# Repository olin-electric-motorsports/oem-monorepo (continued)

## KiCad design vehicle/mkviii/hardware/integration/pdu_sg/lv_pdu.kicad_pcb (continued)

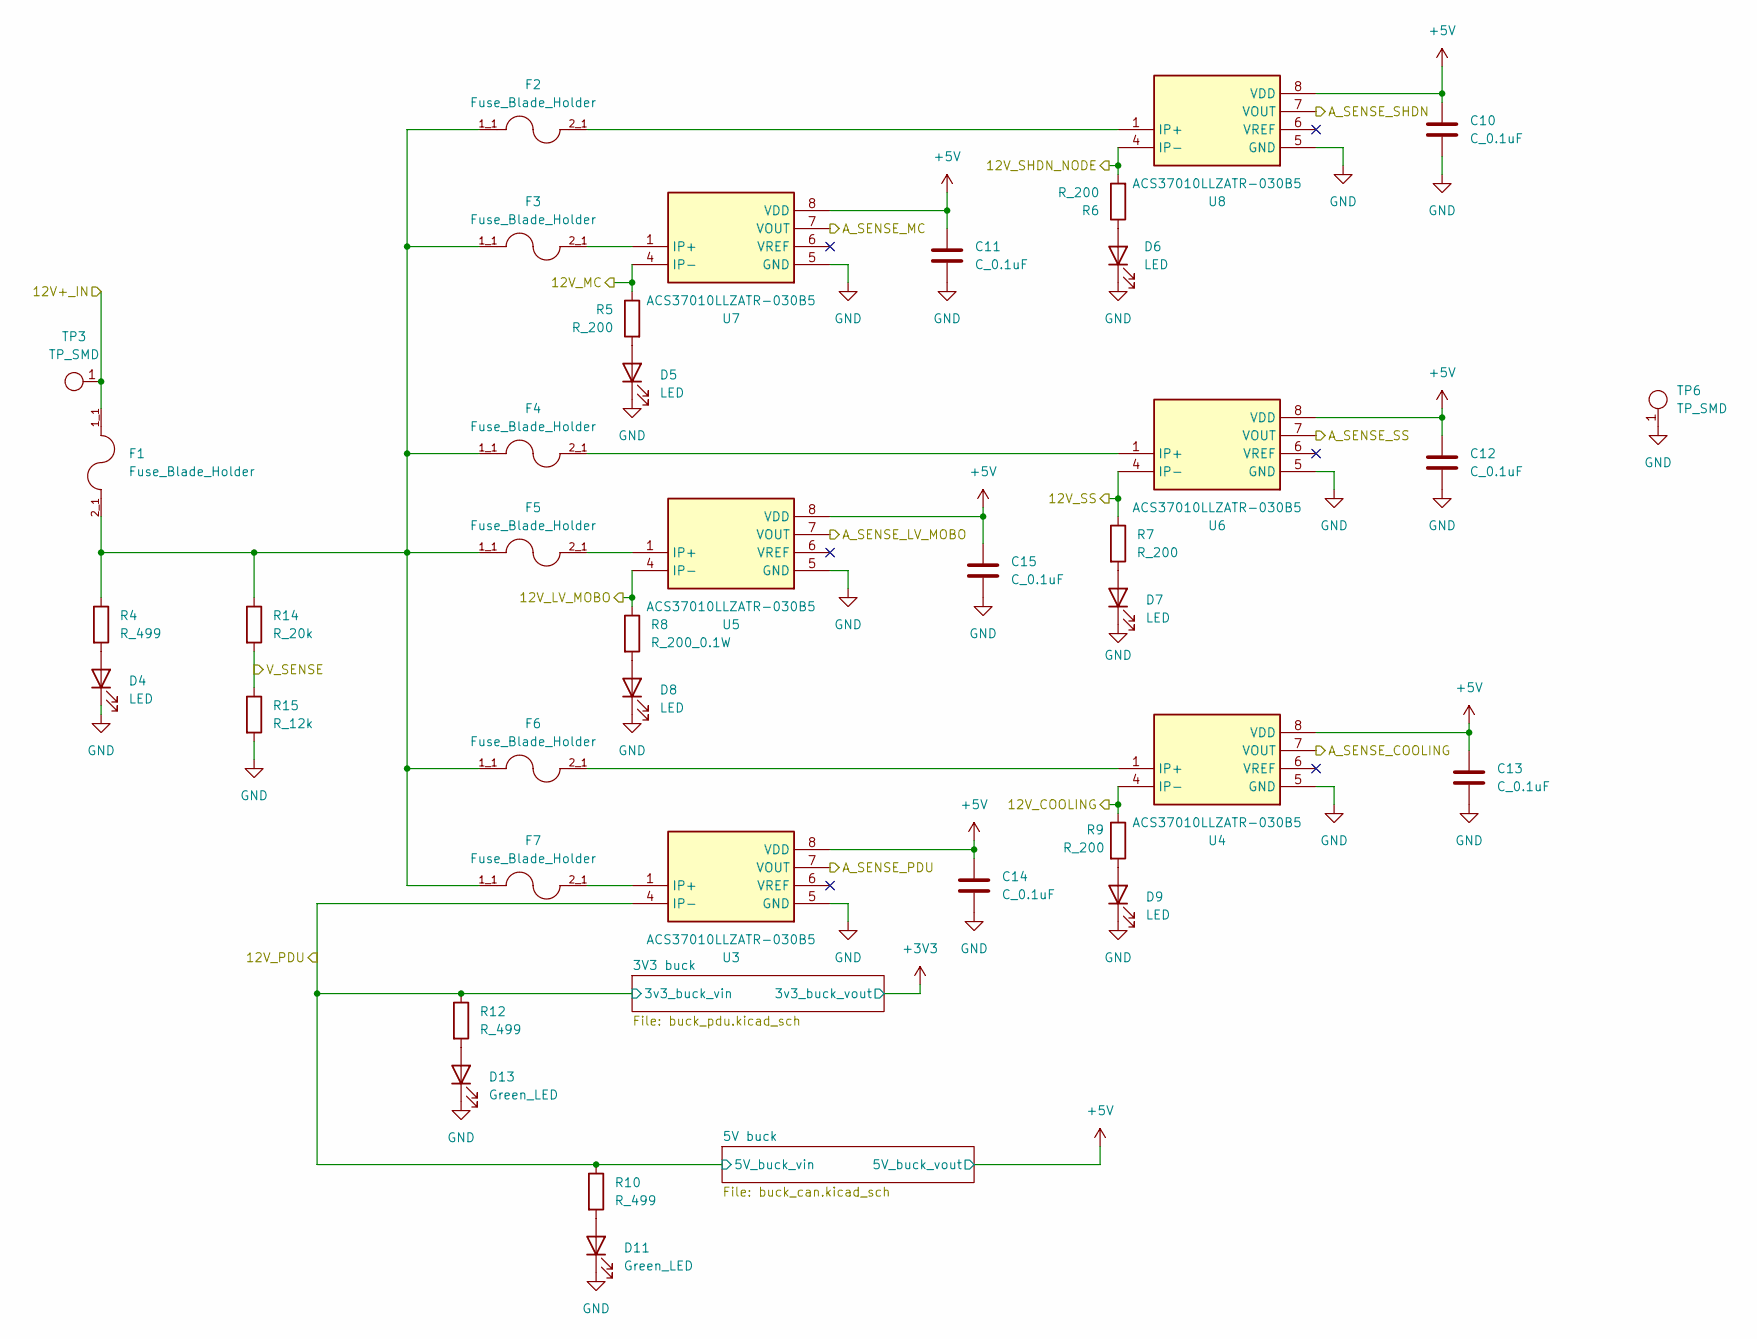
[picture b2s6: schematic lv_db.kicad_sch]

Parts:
C10, C11, C12, C13, C14, C15: C_0.1uF; C_0603_1608Metric; MPN CL10B104KB8NNWC
D4, D5, D6, D7, D8, D9: LED; D_0805_2012Metric
D11, D13: Green_LED; D_0805_2012Metric; MPN LTST-C170KGKT
F1, F2, F3, F4, F5, F6, F7: Fuse_Blade_Holder; MPN 3557-2
R4, R10, R12: R_499; R_0603_1608Metric; MPN RC0603FR-10499RL
R5, R6, R7, R9: R_200; R_0603_1608Metric; MPN WR06X2000FTL
R8: R_200_0.1W; R_0603_1608Metric; MPN WR06X2000FTL
R14: R_20k; R_0603_1608Metric; MPN SR2512JK-7W20KL
R15: R_12k; R_0603_1608Metric; MPN RMCF0603FT12K0
TP3, TP6: TP_SMD; TP_Hook_SMD; MPN 5019
U3, U4, U5, U6, U7, U8: ACS37010LLZATR-030B5; U_Current-Sensor_ACS37010LLZATR-030B5_SOIC-6; MPN ACS37010LLZATR-030B5

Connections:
+5V: C10.1, C11.1, C12.1, C13.1, C14.1, C15.1, U3.8 (VDD), U4.8 (VDD), U5.8 (VDD), U6.8 (VDD), U7.8 (VDD), U8.8 (VDD); also elsewhere on the board
+12V: F1.1, F1.1_1, F1.1_2, TP3.1; also elsewhere on the board
/12V_COOLING: R9.1, U4.4 (IP-); also elsewhere on the board
/12V_LV: R8.1, U5.4 (IP-); also elsewhere on the board
/12V_MC: R5.1, U7.4 (IP-); also elsewhere on the board
/12V_SHDN: R6.2, U8.4 (IP-); also elsewhere on the board
/12V_SS: R7.1, U6.4 (IP-); also elsewhere on the board
/AS_COOL: U4.7 (VOUT); also elsewhere on the board
/AS_LV: U5.7 (VOUT); also elsewhere on the board
/AS_MC: U7.7 (VOUT); also elsewhere on the board
/AS_PDU: U3.7 (VOUT); also elsewhere on the board
/AS_SHDN: U8.7 (VOUT); also elsewhere on the board
/AS_SS: U6.7 (VOUT); also elsewhere on the board
/V_SENSE: R14.2, R15.1; also elsewhere on the board
GND: C10.2, C11.2, C12.2, C13.2, C14.2, C15.2, D4.1 (K), D5.1 (K), D6.1 (K), D7.1 (K), D8.1 (K), D9.1 (K), D11.1 (K), D13.1 (K), R15.2, TP6.1, U3.5 (GND), U4.5 (GND), U5.5 (GND), U6.5 (GND), U7.5 (GND), U8.5 (GND); also elsewhere on the board
unnamed: D4.2 (A), R4.2
unnamed: D5.2 (A), R5.2
unnamed: D6.2 (A), R6.1
unnamed: D7.2 (A), R7.2
unnamed: D8.2 (A), R8.2
unnamed: D9.2 (A), R9.2
unnamed: D11.2 (A), R10.2
unnamed: D13.2 (A), R12.2
unnamed: F1.2, F1.2_1, F1.2_2, F2.1, F2.1_1, F2.1_2, F3.1, F3.1_1, F3.1_2, F4.1, F4.1_1, F4.1_2, F5.1, F5.1_1, F5.1_2, F6.1, F6.1_1, F6.1_2, F7.1, F7.1_1, F7.1_2, R4.1, R14.1
unnamed: F7.2, F7.2_1, F7.2_2, U3.1 (IP+)
unnamed: F6.2, F6.2_1, F6.2_2, U4.1 (IP+)
unnamed: F5.2, F5.2_1, F5.2_2, U5.1 (IP+)
unnamed: F4.2, F4.2_1, F4.2_2, U6.1 (IP+)
unnamed: F3.2, F3.2_1, F3.2_2, U7.1 (IP+)
unnamed: F2.2, F2.2_1, F2.2_2, U8.1 (IP+)

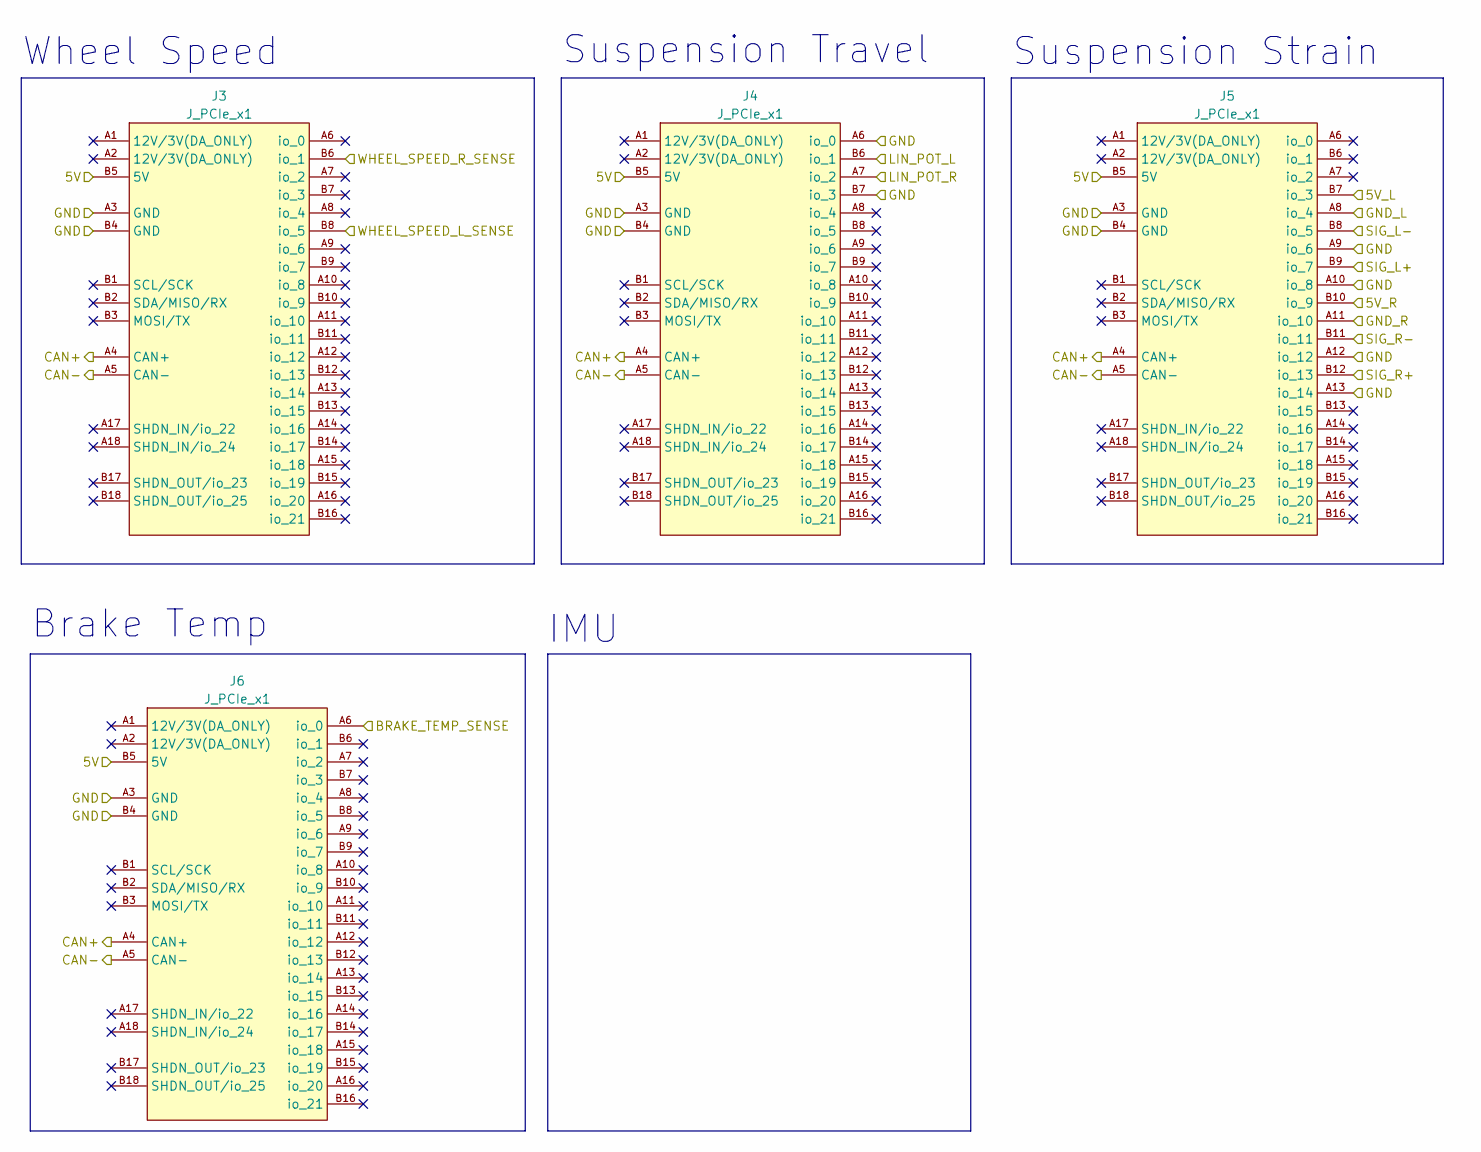
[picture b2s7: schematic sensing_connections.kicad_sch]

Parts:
J3, J4, J5, J6: J_PCIe_x1; MPN 2-1761465-1

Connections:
+5V: J3.B5 (5V), J4.B5 (5V), J5.B5 (5V), J6.B5 (5V); also elsewhere on the board
/BRAKE_TEMP_SIG: J6.A6 (io_0); also elsewhere on the board
/CAN_2+: J3.A4 (CAN+), J4.A4 (CAN+), J5.A4 (CAN+), J6.A4 (CAN+); also elsewhere on the board
/CAN_2-: J3.A5 (CAN-), J4.A5 (CAN-), J5.A5 (CAN-), J6.A5 (CAN-); also elsewhere on the board
/EXCITATION_L+: J5.B7 (io_3); also elsewhere on the board
/EXCITATION_L-: J5.A8 (io_4); also elsewhere on the board
/EXCITATION_R+: J5.B10 (io_9); also elsewhere on the board
/EXCITATION_R-: J5.A11 (io_10); also elsewhere on the board
/SIGNAL_L+: J5.B9 (io_7); also elsewhere on the board
/SIGNAL_L-: J5.B8 (io_5); also elsewhere on the board
/SIGNAL_R+: J5.B12 (io_13); also elsewhere on the board
/SIGNAL_R-: J5.B11 (io_11); also elsewhere on the board
/SUS_TRAVEL_L_SIG: J4.B6 (io_1); also elsewhere on the board
/SUS_TRAVEL_R_SIG: J4.A7 (io_2); also elsewhere on the board
/WHEEL_SPEED_L_SIG: J3.B8 (io_5)
/WHEEL_SPEED_R_SIG: J3.B6 (io_1)
GND: J3.A3 (GND), J3.B4 (GND), J4.A3 (GND), J4.A6 (io_0), J4.B4 (GND), J4.B7 (io_3), J5.A3 (GND), J5.A9 (io_6), J5.A10 (io_8), J5.A12 (io_12), J5.A13 (io_14), J5.B4 (GND), J6.A3 (GND), J6.B4 (GND); also elsewhere on the board

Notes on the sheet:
Brake Temp
Suspension Travel
IMU
Suspension Strain
Wheel Speed

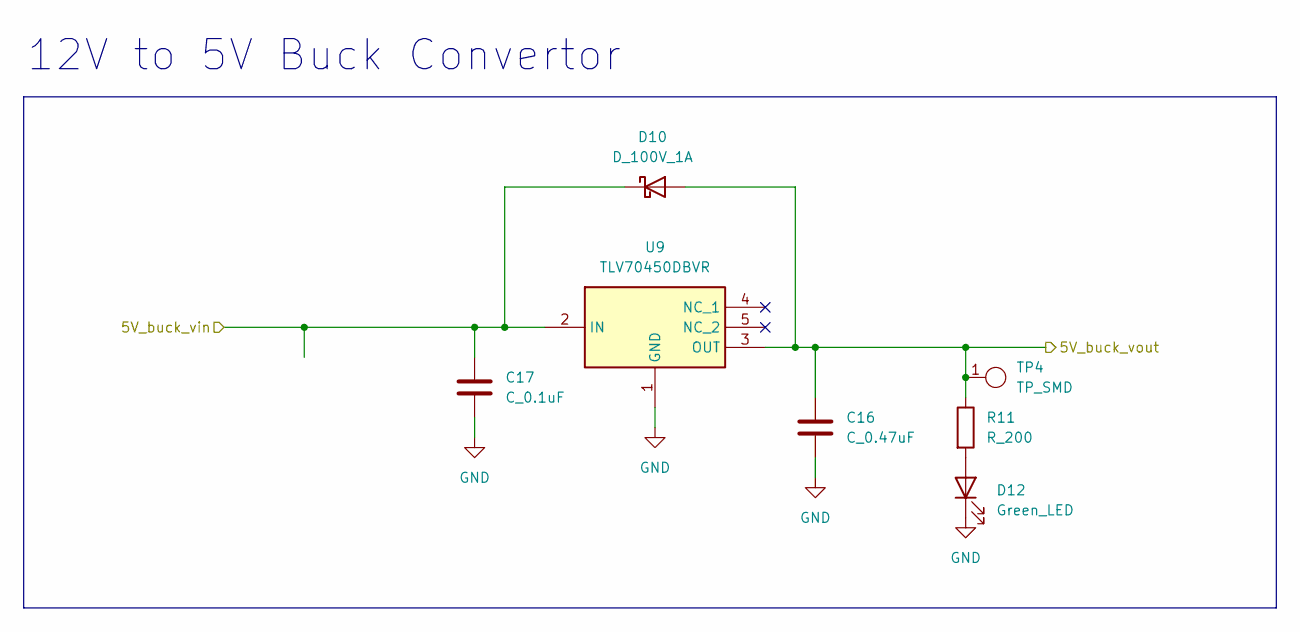
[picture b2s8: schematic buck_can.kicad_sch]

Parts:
C16: C_0.47uF; C_0603_1608Metric; MPN GRM188R71E474KA12D
C17: C_0.1uF; C_0603_1608Metric; MPN C0603C104Z4VACTU
D10: D_100V_1A; SODFL3718X102N (D_Schottky_100V_1A_SMD - SS110LW); MPN SS110LW
D12: Green_LED; D_0805_2012Metric; MPN LTST-C171KRKT
R11: R_200; R_0603_1608Metric; MPN WR06X2000FTL
TP4: TP_SMD; TP_Hook_SMD; MPN 5019
U9: TLV70450DBVR; SOT-23-5; MPN TLV70450DBVR

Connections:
+5V: C16.1, D10.2 (A), R11.1, TP4.1, U9.3 (OUT); also elsewhere on the board
GND: C16.2, C17.2, D12.1 (K), U9.1 (GND); also elsewhere on the board
unnamed: D12.2 (A), R11.2

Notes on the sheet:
12V to 5V Buck Convertor

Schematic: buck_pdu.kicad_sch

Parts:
C18: C_10uF; C_0603_1608Metric; MPN GRM188D71A106KA73D
C19, C20: C_22uF; C_0603_1608Metric; MPN CL31A226KAHNNNE
C21: C_0.1uF; C_0603_1608Metric; MPN C0603C104Z4VACTU
D14: Green_LED; D_0805_2012Metric; MPN LTST-C170KGKT
L1: L_3.9uH; IND_BOURNS_SRR5018 (L_3.9uH_2A_55m_SMD); MPN SRR5018-3R9Y
R13: R_60.4; R_0603_1608Metric; MPN RMCF0603FT60R4
TP5: TP_SMD; TP_Hook_SMD; MPN 5019
U10: AP63203WU-7; SOT-23-6; MPN AP63203WU-7

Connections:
/low voltage distribution/3V3 buck/3V3_buck_vout: C19.1, C20.1, L1.2, R13.1, TP5.1, U10.1 (FB)
GND: C18.2, C19.2, C20.2, D14.1 (K), U10.4 (GND); also elsewhere on the board
unnamed: D14.2 (A), R13.2
unnamed: C21.1, U10.6 (BST)
unnamed: C21.2, L1.1, U10.5 (SW)

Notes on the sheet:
12V to 3V3 Buck Converter

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
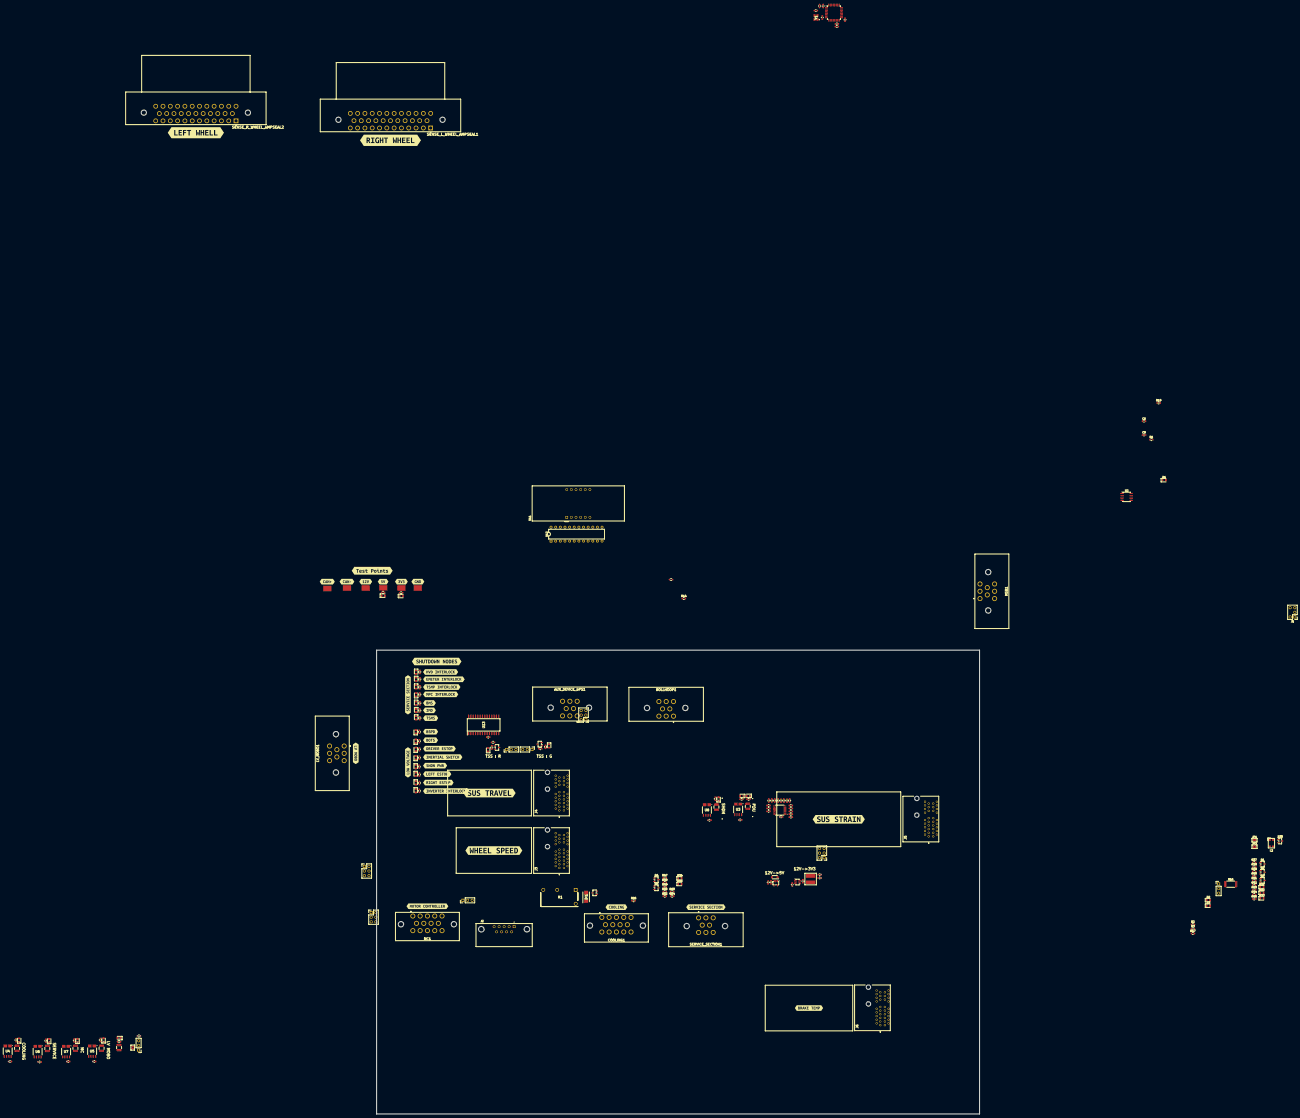
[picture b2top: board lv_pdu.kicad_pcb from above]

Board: 4 copper layers, 330.2 x 254.0 mm, 233 parts (0 on the bottom side), 167 nets.

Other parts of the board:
kibuzzard-6AF3A9EF: G***; kibuzzard-6AF3A9EF
kibuzzard-6AF3AA3E: G***; kibuzzard-6AF3AA3E
kibuzzard-6AF3AA7C: G***; kibuzzard-6AF3AA7C
kibuzzard-6AF3AA54: G***; kibuzzard-6AF3AA54
kibuzzard-6AF3AA92: G***; kibuzzard-6AF3AA92
kibuzzard-6AF3AAA2: G***; kibuzzard-6AF3AAA2
kibuzzard-6AF3AB1F: G***; kibuzzard-6AF3AB1F
kibuzzard-6AF3AB02: G***; kibuzzard-6AF3AB02
kibuzzard-6AF3AB16: G***; kibuzzard-6AF3AB16
kibuzzard-6AF3AB30: G***; kibuzzard-6AF3AB30
kibuzzard-6AF3AC5A: G***; kibuzzard-6AF3AC5A
kibuzzard-6AF3AC21: G***; kibuzzard-6AF3AC21
kibuzzard-6AF3AC46: G***; kibuzzard-6AF3AC46
kibuzzard-6AF3AC51: G***; kibuzzard-6AF3AC51
kibuzzard-6AF3AC73: G***; kibuzzard-6AF3AC73
kibuzzard-6AF3AC82: G***; kibuzzard-6AF3AC82
kibuzzard-6AF3ACA7: G***; kibuzzard-6AF3ACA7
kibuzzard-6AF3ACE3: G***; kibuzzard-6AF3ACE3
kibuzzard-6AF3AD90: G***; kibuzzard-6AF3AD90
kibuzzard-6AF3ADBE: G***; kibuzzard-6AF3ADBE
kibuzzard-6AF3ADF4: G***; kibuzzard-6AF3ADF4
kibuzzard-6AF3AE7A: G***; kibuzzard-6AF3AE7A
kibuzzard-6AF3AE17: G***; kibuzzard-6AF3AE17
kibuzzard-6AF3AEED: G***; kibuzzard-6AF3AEED
kibuzzard-6AF3AF2F: G***; kibuzzard-6AF3AF2F
kibuzzard-6AF3BEE3: G***; kibuzzard-6AF3BEE3
kibuzzard-6AF3BF1E: G***; kibuzzard-6AF3BF1E
kibuzzard-6AF3BF40: G***; kibuzzard-6AF3BF40
kibuzzard-6AF392A3: G***; kibuzzard-6AF392A3
kibuzzard-6AF392F1: G***; kibuzzard-6AF392F1
kibuzzard-6AF3934F: G***; kibuzzard-6AF3934F
kibuzzard-6AF3939E: G***; kibuzzard-6AF3939E
kibuzzard-6AF39264: G***; kibuzzard-6AF39264
kibuzzard-6AF39337: G***; kibuzzard-6AF39337
kibuzzard-6AF39365: G***; kibuzzard-6AF39365

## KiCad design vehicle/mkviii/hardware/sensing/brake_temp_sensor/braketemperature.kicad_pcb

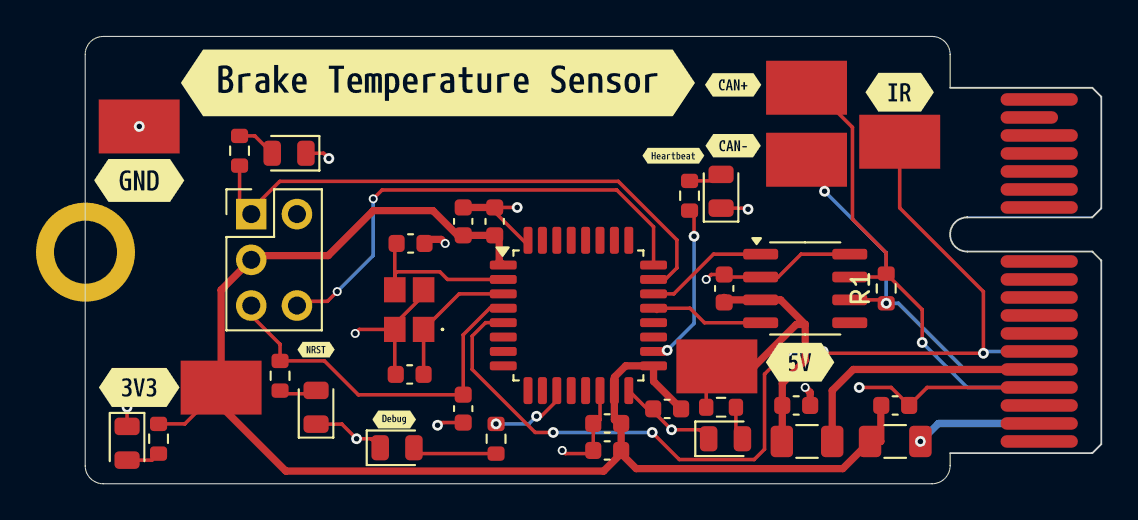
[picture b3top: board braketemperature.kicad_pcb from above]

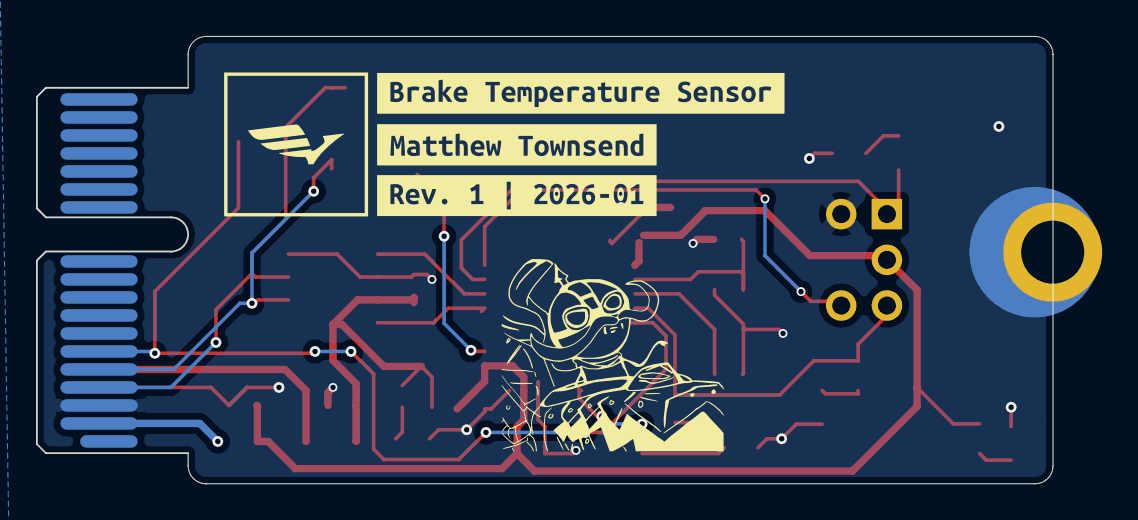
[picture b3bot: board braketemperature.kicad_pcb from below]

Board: 2 copper layers, 56.4 x 24.9 mm, 51 parts (3 on the bottom side), 23 nets.

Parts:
C1, C2, C4, C7: C_0.1uF; C_0603_1608Metric
C3: C_10nF; C_0603_1608Metric
C5: C_1uF; C_0603_1608Metric
C6: C_4.7uF; C_0603_1608Metric
C8, C9: C_30pF; C_0603_1608Metric
C10, C11: C_10uF_10V; C_0603_1608Metric
D1, D2, D3, D4, D5, D6: D_Red_LED; D_0805_2012Metric
F1, F2: F_500mA_8V; Fuse_1206_3216Metric
H1: H_MountingHole
J1: J_PCIe_x1; J_PCIe_x1_Key
J2: J_Programming_Pin_Header; J_Programming_Pin_Header_Keyed
R1: R_120; R_0603_1608Metric
R2, R3, R4, R5, R6, R7: R_1k; R_0603_1608Metric
TP1, TP2, TP3, TP4, TP5, TP6: TP_SMD; TP_Hook_SMD
U1: MCP2561-E_SN; SOIC-8_3.9x4.9mm_P1.27mm
U2: STM32G441KBT6; LQFP-32_7x7mm_P0.8mm
Y1: X_16MHz_18pF; FA238160000MBC0 (X_16MHz_18pF_SMD - FA-238_16.0000MB-C0)
kibuzzard-697E6E94: G***; kibuzzard-697E6E94
kibuzzard-697E6EEF: G***; kibuzzard-697E6EEF
kibuzzard-697E6F70: G***; kibuzzard-697E6F70
kibuzzard-697E6FE4: G***; kibuzzard-697E6FE4
kibuzzard-697F80A9: G***; kibuzzard-697F80A9
kibuzzard-697F80BA: G***; kibuzzard-697F80BA
kibuzzard-697F802E: G***; kibuzzard-697F802E
kibuzzard-69815F9D: G***; kibuzzard-69815F9D
kibuzzard-69815FEC: G***; kibuzzard-69815FEC
kibuzzard-69815FF8: G***; kibuzzard-69815FF8
kibuzzard-69816079: G***; kibuzzard-69816079
kibuzzard-69816083: G***; kibuzzard-69816083
kibuzzard-69816091: G***; kibuzzard-69816091

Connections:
+3V3: C2.1, C3.1, C4.1, C5.1, C6.1, C11.1, F2.1, J2.3, R3.1, TP3.1, U2.1 (VDD), U2.15 (VDDA), U2.17 (VDD)
+5V: C1.1, C10.1, F1.1, R2.1, TP2.1, U1.3 (VDD)
/CAN_RX: U1.4 (RXD), U2.21 ((FDCAN1_RX/GPIO_EXTI11)PA11)
/CAN_TX: U1.1 (TXD), U2.22 ((FDCAN1_TX/GPIO_EXTI12)PA12)
/Debug LED: R5.1, U2.11 ((TIM3_CH1/TIM16_CH1/GPIO_EXTI6/ADC2_IN3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)
/Heartbeat LED: R4.1, U2.18 ((TIM4_ETR/USART1_CK/GPIO_EXTI8)PA8)
/IR Output - PA0: J1.A6 (io_0), TP1.1, U2.5 ((TIM2_ETR/TIM2_CH1/GPIO_EXTI0/ADC2_IN1/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)
/NRST: C7.1, J2.4, R6.1, U2.4 ((GPIO_EXTI10)PG10-NRST)
/SWCLK: J2.5, U2.24 ((SYS_JTCK-SWCLK/GPIO_EXTI14)PA14)
/SWDIO: J2.1, R7.1, U2.23 ((SYS_JTMS-SWDIO/GPIO_EXTI13)PA13)
GND: C1.2, C2.2, C3.2, C4.2, C5.2, C6.2, C7.2, C8.2, C9.2, C10.2, C11.2, D1.1 (K), D2.1 (K), D3.1 (K), D4.1 (K), D5.1 (K), D6.1 (K), H1.1, J1.A3 (GND), J1.B4 (GND), J2.2, TP6.1, U1.2 (VSS), U1.8 (STBY), U2.14 (VSSA), U2.16 (VSS), U2.32 (VSS), Y1.2, Y1.4
unnamed: D1.2 (A), R2.2
unnamed: D2.2 (A), R3.2
unnamed: D3.2 (A), R4.2
unnamed: D4.2 (A), R5.2
unnamed: D5.2 (A), R6.2
unnamed: D6.2 (A), R7.2
unnamed: F2.2, J1.A2 (3.3V)
unnamed: F1.2, J1.B5 (5V)
unnamed: J1.A4 (CAN+), R1.2, TP4.1, U1.7 (CANH)
unnamed: J1.A5 (CAN-), R1.1, TP5.1, U1.6 (CANL)
unnamed: C9.1, U2.2 (PF0-OSC_IN), Y1.3
unnamed: C8.1, U2.3 (PF1-OSC_OUT), Y1.1

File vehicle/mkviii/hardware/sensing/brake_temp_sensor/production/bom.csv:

Designator,Footprint,Quantity,Value,LCSC Part #
"C1, C2, C4, C7",0603,4,C_0.1uF,C0603C104Z4VACTU
"C10, C11",0603,2,C_10uF_10V,GRM188D71A106KA73D
C3,0603,1,C_10nF,CL10B103KB8NNNC
C5,0603,1,C_1uF,CL10B105KA8NNNC
C6,0603,1,C_4.7uF,GRT188R61E475ME13D
"C8, C9",0603,2,C_30pF,CML0603C0G300JT50V
"D1, D2, D3, D4, D5, D6",0805,6,D_Red_LED,LTST-C171KRKT
"F1, F2",1206,2,F_500mA_8V,0ZCJ0050FF2G
J1,J_PCIe_x1_Key,1,J_PCIe_x1,2-1761465-1
J2,J_Programming_Pin_Header_Keyed,1,J_Programming_Pin_Header,
R1,0603,1,R_120,RC0603FR-13120RL
"R2, R3, R4, R5, R6, R7",0603,6,R_1k,RMCF0603FT1K00 (or ERJ-3GEYJ102V)
"TP1, TP2, TP3, TP4, TP5, TP6",TP_Hook_SMD,6,TP_SMD,5019
U1,SOIC-8_3.9x4.9mm_P1.27mm,1,MCP2561-E_SN,MCP2561-E/SN
U2,LQFP-32_7x7mm_P0.8mm,1,STM32G441KBT6,
Y1,FA238160000MBC0 (X_16MHz_18pF_SMD - FA-238_16.0000MB-C0),1,X_16MHz_18pF,FA-238 16.0000MB-C0

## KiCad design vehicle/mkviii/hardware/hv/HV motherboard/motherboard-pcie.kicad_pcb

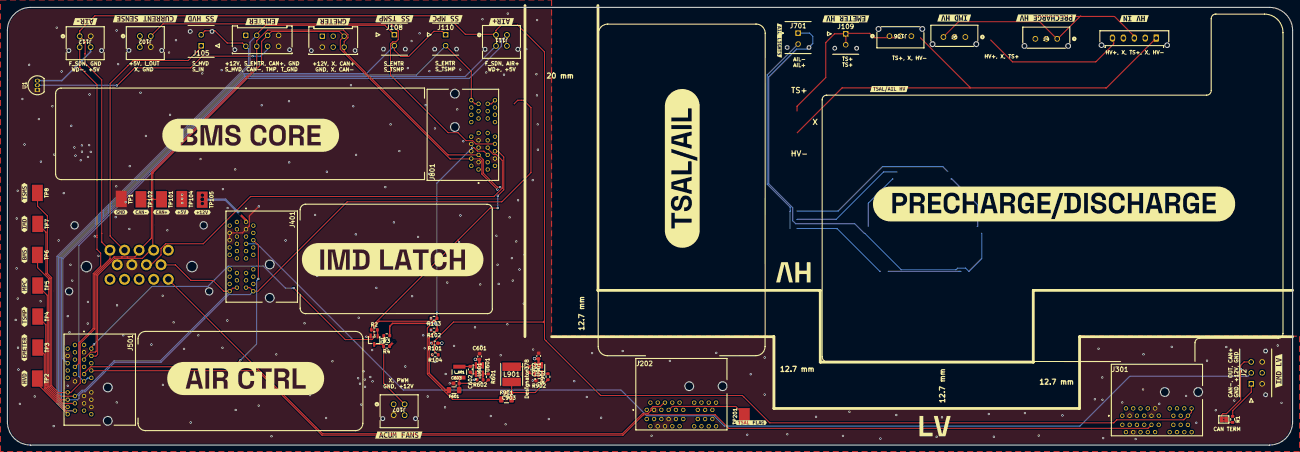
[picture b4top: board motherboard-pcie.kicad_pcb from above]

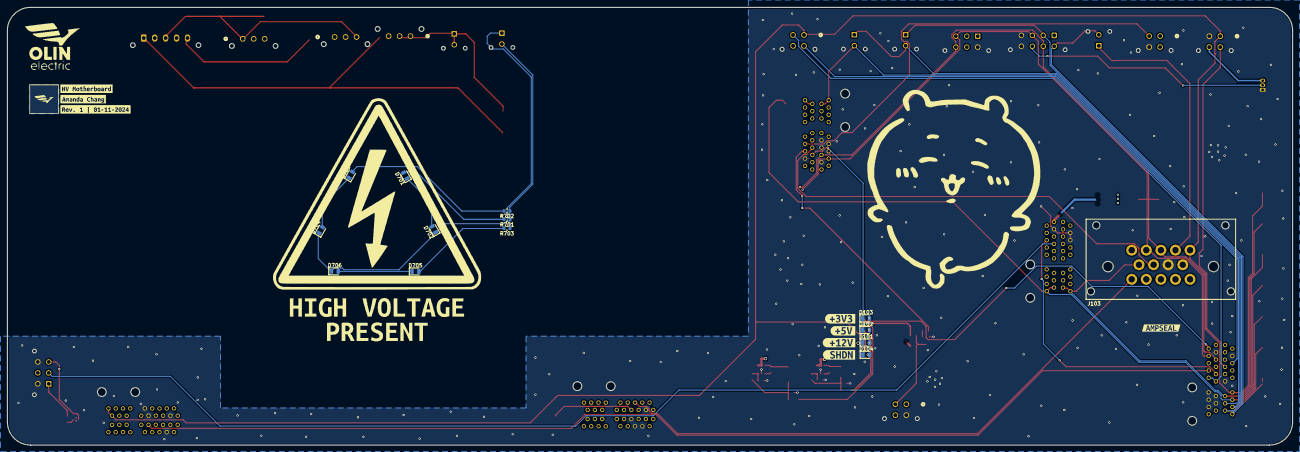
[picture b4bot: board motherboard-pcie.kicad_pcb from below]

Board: 4 copper layers, 352.4 x 120.0 mm, 121 parts (24 on the bottom side), 52 nets.

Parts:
C601, C901: C_2.2uF; C_0603_1608Metric
C602, C902: C_0.1uF; C_0603_1608Metric
C603, C903: C_10uF; C_0603_1608Metric
D101, D102: D_Green_LED; D_0805_2012Metric
D103: LED; D_0805_2012Metric
D104: D_Blue_LED; D_0805_2012Metric
D701, D702, D703, D704, D705, D706: LED_0805; D_0805_2012Metric
F601, F901: F_1.5A_63V; Fuse_1206_3216Metric
J1: Conn_02x04_Odd_Even; Molex_Micro-Fit_3.0_43045-0812_2x04_P3.00mm_Vertical
J2: 2X3; J_Molex_Header_02x03_VT - 43045-06YY_121314
J3: Conn_01x05; Molex_Micro-Fit_3.0_43650-0515_1x05_P3.00mm_Vertical
J4, J6, J106: J_Molex_Header_01x03_VT; J_Molex_Header_01x03_VT - 436500327
J102, J111, J112: AIR+; J_Molex_Header_02x02_VT - 0430450414
J103: J_Ampseal_14_VT
J105, J108, J109, J110, J701: J_Molex_Header_01x02_VT; J_Molex_Header_01x02_VT - 43045-02YY_121314
J107: ACCUM_FAN; J_Molex_Header_02x02_VT - 0430450414
J113: GMETER; Molex_Micro-Fit_3.0_43045-0612_2x03_P3.00mm_Vertical
J202, J301, J401, J501, J801: J_PCIe_x1
JP1: SolderJumper_2_Bridged; SolderJumper-2_P1.3mm_Bridged2Bar_Pad1.0x1.5mm
L901: L_3.3uH; SRN6045TA330M (L_3.3uH_5A_21m_SMD - SRN6045TA-3R3Y)
L_601: L_4.7uH; IND_ASPI-4030S-4R7M-T
Q1: SSM3K333R,LF; SOT-23-3
R1, R701, R702, R703: R_120; R_0603_1608Metric
R2, R3, R4: R_100; R_0603_1608Metric
R101, R104: R_1k; R_0603_1608Metric
R102: R_330; R_0603_1608Metric
R103: R_301; R_0603_1608Metric
R601: R_88.7k; R_0603_1608Metric
R602, R902: R_22.1k; R_0603_1608Metric
R901: R_51k; R_0603_1608Metric
TP1, TP2, TP3, TP4, TP5, TP6, TP7, TP8, TP101, TP102, TP104, TP105, TP201: TP_SMD; TP_Hook_SMD
U1: DS18B20; TO-92_Inline
U601: U_5V-Buck-Conv-1A-SOT23-6; DBV0006A-IPC_A
U901: U_3.3V-Buck-Conv-1A-SOT23-6; DBV0006A-IPC_A
kibuzzard-6AF3C239: G***; kibuzzard-6AF3C239
kibuzzard-6AF3C241: G***; kibuzzard-6AF3C241
kibuzzard-640B75B2: G***; kibuzzard-640B75B2
kibuzzard-640B76B0: G***; kibuzzard-640B76B0
kibuzzard-640B87CD: G***; kibuzzard-640B87CD
kibuzzard-640B861F: G***; kibuzzard-640B861F
kibuzzard-640B8645: G***; kibuzzard-640B8645
kibuzzard-640B8668: G***; kibuzzard-640B8668
kibuzzard-640B8680: G***; kibuzzard-640B8680
kibuzzard-677B3C3E: G***; kibuzzard-677B3C3E
kibuzzard-677B3C38: G***; kibuzzard-677B3C38
kibuzzard-677B3E90: G***; kibuzzard-677B3E90
kibuzzard-677CE749: G***; kibuzzard-677CE749
kibuzzard-677CFB84: G***; kibuzzard-677CFB84
kibuzzard-677CFB97: G***; kibuzzard-677CFB97
kibuzzard-677CFBA0: G***; kibuzzard-677CFBA0
kibuzzard-677E2BD4: G***; kibuzzard-677E2BD4
kibuzzard-677E2BDC: G***; kibuzzard-677E2BDC
kibuzzard-677E2BE2: G***; kibuzzard-677E2BE2
kibuzzard-677E2BE7: G***; kibuzzard-677E2BE7
kibuzzard-677E2BEC: G***; kibuzzard-677E2BEC
kibuzzard-677E2BF5: G***; kibuzzard-677E2BF5
kibuzzard-677E2BFE: G***; kibuzzard-677E2BFE
kibuzzard-677E26A9: G***; kibuzzard-677E26A9
kibuzzard-677E26B0: G***; kibuzzard-677E26B0
kibuzzard-677E26B5: G***; kibuzzard-677E26B5
kibuzzard-677E26BE: G***; kibuzzard-677E26BE
kibuzzard-677E26C5: G***; kibuzzard-677E26C5
kibuzzard-677E26CB: G***; kibuzzard-677E26CB
kibuzzard-677E26D4: G***; kibuzzard-677E26D4
kibuzzard-677E26ED: G***; kibuzzard-677E26ED
kibuzzard-677E335B: G***; kibuzzard-677E335B
kibuzzard-677E336E: G***; kibuzzard-677E336E
kibuzzard-677E3331: G***; kibuzzard-677E3331
kibuzzard-677E3355: G***; kibuzzard-677E3355
kibuzzard-677E3368: G***; kibuzzard-677E3368
kibuzzard-677FDCF4: G***; kibuzzard-677FDCF4
kibuzzard-6786FEE0: G***; kibuzzard-6786FEE0
kibuzzard-6786FEEF: G***; kibuzzard-6786FEEF
kibuzzard-678236F4: G***; kibuzzard-678236F4
kibuzzard-678238A8: G***; kibuzzard-678238A8
kibuzzard-678249D1: G***; kibuzzard-678249D1
kibuzzard-678771B8: G***; kibuzzard-678771B8
kibuzzard-67823702: G***; kibuzzard-67823702
kibuzzard-67823719: G***; kibuzzard-67823719
kibuzzard-67878439: G***; kibuzzard-67878439

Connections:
+3.3V: F901.1, J501.A2 (12V/3V(DA_ONLY)), J801.B5 (5V), R103.1
+5V: F601.1, J102.1, J111.4, J112.4, J202.B5 (5V), J401.B5 (5V), J501.B5 (5V), J801.A2 (12V/3V(DA_ONLY)), R3.1, R102.1, TP104.1, U1.3 (V_{DD})
+12V: C601.1, C901.1, J1.1, J2.5, J103.9, J103.11, J107.4, J113.1, J202.A1 (12V/3V(DA_ONLY)), J401.A1 (12V/3V(DA_ONLY)), R4.1, R101.1, TP105.1, U601.4 (EN), U601.5 (VIN), U901.4 (EN), U901.5 (VIN)
/AIR+_LSD: J111.2, J501.A10 (io_8), J501.A11 (io_10)
/AIR+_WELD_DETECT: J111.3, J501.B6 (io_1)
/AIR-_WELD_DETECT: J112.3, J501.B7 (io_3)
/BSPD_CURRENT_THRESH: J103.7, J801.B7 (io_3)
/CAN+: J1.3, J2.3, J103.2, J113.3, J501.A4 (CAN+), J801.A4 (CAN+), JP1.1 (A), TP101.1
/CAN-: J1.6, J2.1, J103.3, J113.6, J501.A5 (CAN-), J801.A5 (CAN-), R1.1, TP102.1
/EMETER_TEMP: J1.7, U1.2 (DQ)
/FAN_PWM: J801.B6 (io_1), R2.1
/FINAL_SHDN: J103.5, J111.1, J112.1, J301.A17 (SHDN_IN/io_22), J301.A18 (SHDN_IN/io_24), J501.B12 (io_13), R104.1, TP8.1
/HV_AIL_-: J3.1, J6.1, J106.3
/HV_BAT_+: J3.5, J4.3
/HV_TS_+_FUSED: J3.3, J4.1, J6.3, J106.1, J109.1, J109.2
/IMD_OUTPUT: J2.2, J401.A7 (io_2)
/IMD_STATUS: J401.A6 (io_0), J501.A9 (io_6)
/PRECHARGE_LSD: J301.B9 (io_7), J501.A8 (io_4)
/RTM_LIGHT-: J103.10, J202.A6 (io_0)
/SHDN_IN: J103.4, J105.1
/SHDN_SENSE_BMS: J401.A17 (SHDN_IN/io_22), J401.A18 (SHDN_IN/io_24), J501.B14 (io_17), J801.B17 (SHDN_OUT/io_23), J801.B18 (SHDN_OUT/io_25), TP6.1
/SHDN_SENSE_EMETER: J1.2, J108.1, J501.B17 (SHDN_OUT/io_23), TP3.1
/SHDN_SENSE_HVD: J1.5, J105.2, J501.B18 (SHDN_OUT/io_25), TP2.1
/SHDN_SENSE_IMD: J103.6, J401.B17 (SHDN_OUT/io_23), J401.B18 (SHDN_OUT/io_25), J501.B13 (io_15), TP7.1
/SHDN_SENSE_MPC: J110.2, J501.B15 (io_19), J801.A17 (SHDN_IN/io_22), J801.A18 (SHDN_IN/io_24), TP5.1
/SHDN_SENSE_TSMP: J108.2, J110.1, J501.B16 (io_21), TP4.1
/VOUT_CURRENT_SENSE: J102.2, J801.B8 (io_5)
/tsal-ail/RTM_LIGHT+: J202.A7 (io_2), TP201.1
GND: C601.2, C603.2, C901.2, C903.2, D101.1 (K), D102.1 (K), D103.1 (K), D104.1 (K), J1.4, J1.8, J2.4, J2.6, J102.4, J103.8, J107.3, J112.2, J113.4, J202.A3 (GND), J202.B4 (GND), J202.B6 (io_1), J202.B7 (io_3), J301.A3 (GND), J301.A9 (io_6), J301.A10 (io_8), J301.B4 (GND), J401.A3 (GND), J401.B4 (GND), J401.B6 (io_1), J501.A3 (GND), J501.A12 (io_12), J501.A13 (io_14), J501.A14 (io_16), J501.A15 (io_18), J501.A16 (io_20), J501.B4 (GND), J501.B11 (io_11), J801.A3 (GND), J801.A6 (io_0), J801.A7 (io_2), J801.A8 (io_4), J801.A9 (io_6), J801.B4 (GND), Q1.2 (S), R602.2, R902.2, TP1.1, U1.1 (GND), U601.2 (GND), U901.2 (GND)
unnamed: C603.1, F601.2, L_601.2, R601.1
unnamed: C903.1, F901.2, L901.2, R901.1
unnamed: D101.2 (A), R101.2
unnamed: D102.2 (A), R102.2
unnamed: D103.2 (A), R103.2
unnamed: D104.2 (A), R104.2
unnamed: D701.2 (A), R701.2
unnamed: D701.1 (K), D702.2 (A)
unnamed: D702.1 (K), D704.1 (K), D706.1 (K), J701.1
unnamed: D703.2 (A), R702.2
unnamed: D703.1 (K), D704.2 (A)
unnamed: D705.2 (A), R703.2
unnamed: D705.1 (K), D706.2 (A)
unnamed: J701.2, R701.1, R702.1, R703.1
unnamed: JP1.2 (B), R1.2
unnamed: J107.2, Q1.3 (D), R3.2, R4.2
unnamed: Q1.1 (G), R2.2
unnamed: C602.2, U601.1 (CB)
unnamed: R601.2, R602.1, U601.3 (FB)
unnamed: C602.1, L_601.1, U601.6 (SW)
unnamed: C902.2, U901.1 (CB)
unnamed: R901.2, R902.1, U901.3 (FB)
unnamed: C902.1, L901.1, U901.6 (SW)
